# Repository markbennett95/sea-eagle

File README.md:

# BCA Sea Eagle Distortion

A multi-stage distortion pedal designed in conjunction with Nick Earle. The inspiration was a tight, heavy, Fall out boy-style rhythm tone. It features a dual-gang gain pot, an active 3-band EQ, and several pre-gain tone shaping switches. It is powered by our standard +-15V power supply, and uses a series of current sources to bias the various JFET stages.

## v1.0.0-build
1590BB enclosure with pots for Gain, Bass, Middle, Treble, Volume, and switches for bright, tight/fat, and high/low input gain.

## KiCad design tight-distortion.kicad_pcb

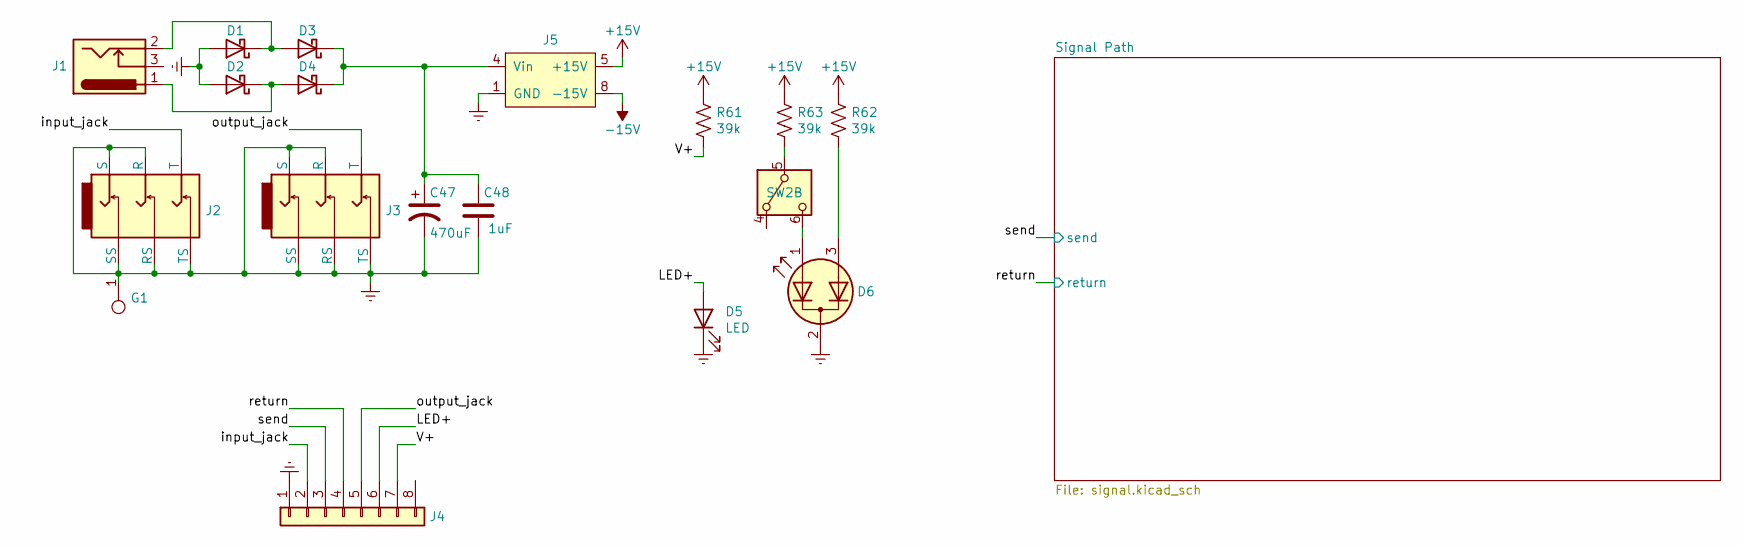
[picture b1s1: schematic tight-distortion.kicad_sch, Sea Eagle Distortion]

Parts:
C47: 470uF; CP_Radial_D8.0mm_P3.50mm
C48: 1uF; C_0805_2012Metric_Pad1.18x1.45mm_HandSolder
D1, D2, D3, D4: 1N5819; D_SOD-123
D5: LED; LED_D5.0mm
D6: LED_Dual_AAK; LED_D5.0mm-3
G1: GNDSpring; Keystone_628
J1: Barrel_Jack_Switch; DC_Jack_DC005
J2, J3: AudioJack_TRS; Rean_NYS215
J4: Conn_01x08; Pin_Header_Straight_1x08_Pitch2.54mm
J5: power-module; Power-module
R61, R62, R63: 39k; R_L3.6mm_D1.6mm_P5.00mm_Horizontal
SW2: SW_DPDT_x2; Pin_Header_Straight_1x06_Pitch2.54mm

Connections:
+15V: J5.5 (+15V), R61.1, R62.1, R63.1; also elsewhere on the board
-15V: J5.8 (-15V); also elsewhere on the board
/LED+: D5.2 (A), J4.6
/V+: J4.7, R61.2
/input_jack: J2.1 (T), J4.2
/output_jack: J3.1 (T), J4.5
/return: J4.4; also elsewhere on the board
/send: J4.3; also elsewhere on the board
Earth: C47.2, C48.2, D1.2 (A), D2.2 (A), D5.1 (K), D6.2 (K), G1.1, J2.2 (R), J2.3 (S), J2.4 (TS), J2.5 (RS), J2.6 (SS), J3.2 (R), J3.3 (S), J3.4 (TS), J3.5 (RS), J3.6 (SS), J4.1, J5.1 (GND); also elsewhere on the board
unnamed: D1.1 (K), D3.2 (A), J1.2
unnamed: D2.1 (K), D4.2 (A), J1.1
unnamed: C47.1, C48.1, D3.1 (K), D4.1 (K), J5.4 (Vin)
unnamed: D6.1 (A1), SW2.6 (C)
unnamed: D6.3 (A2), R62.2
unnamed: R63.2, SW2.5 (B)

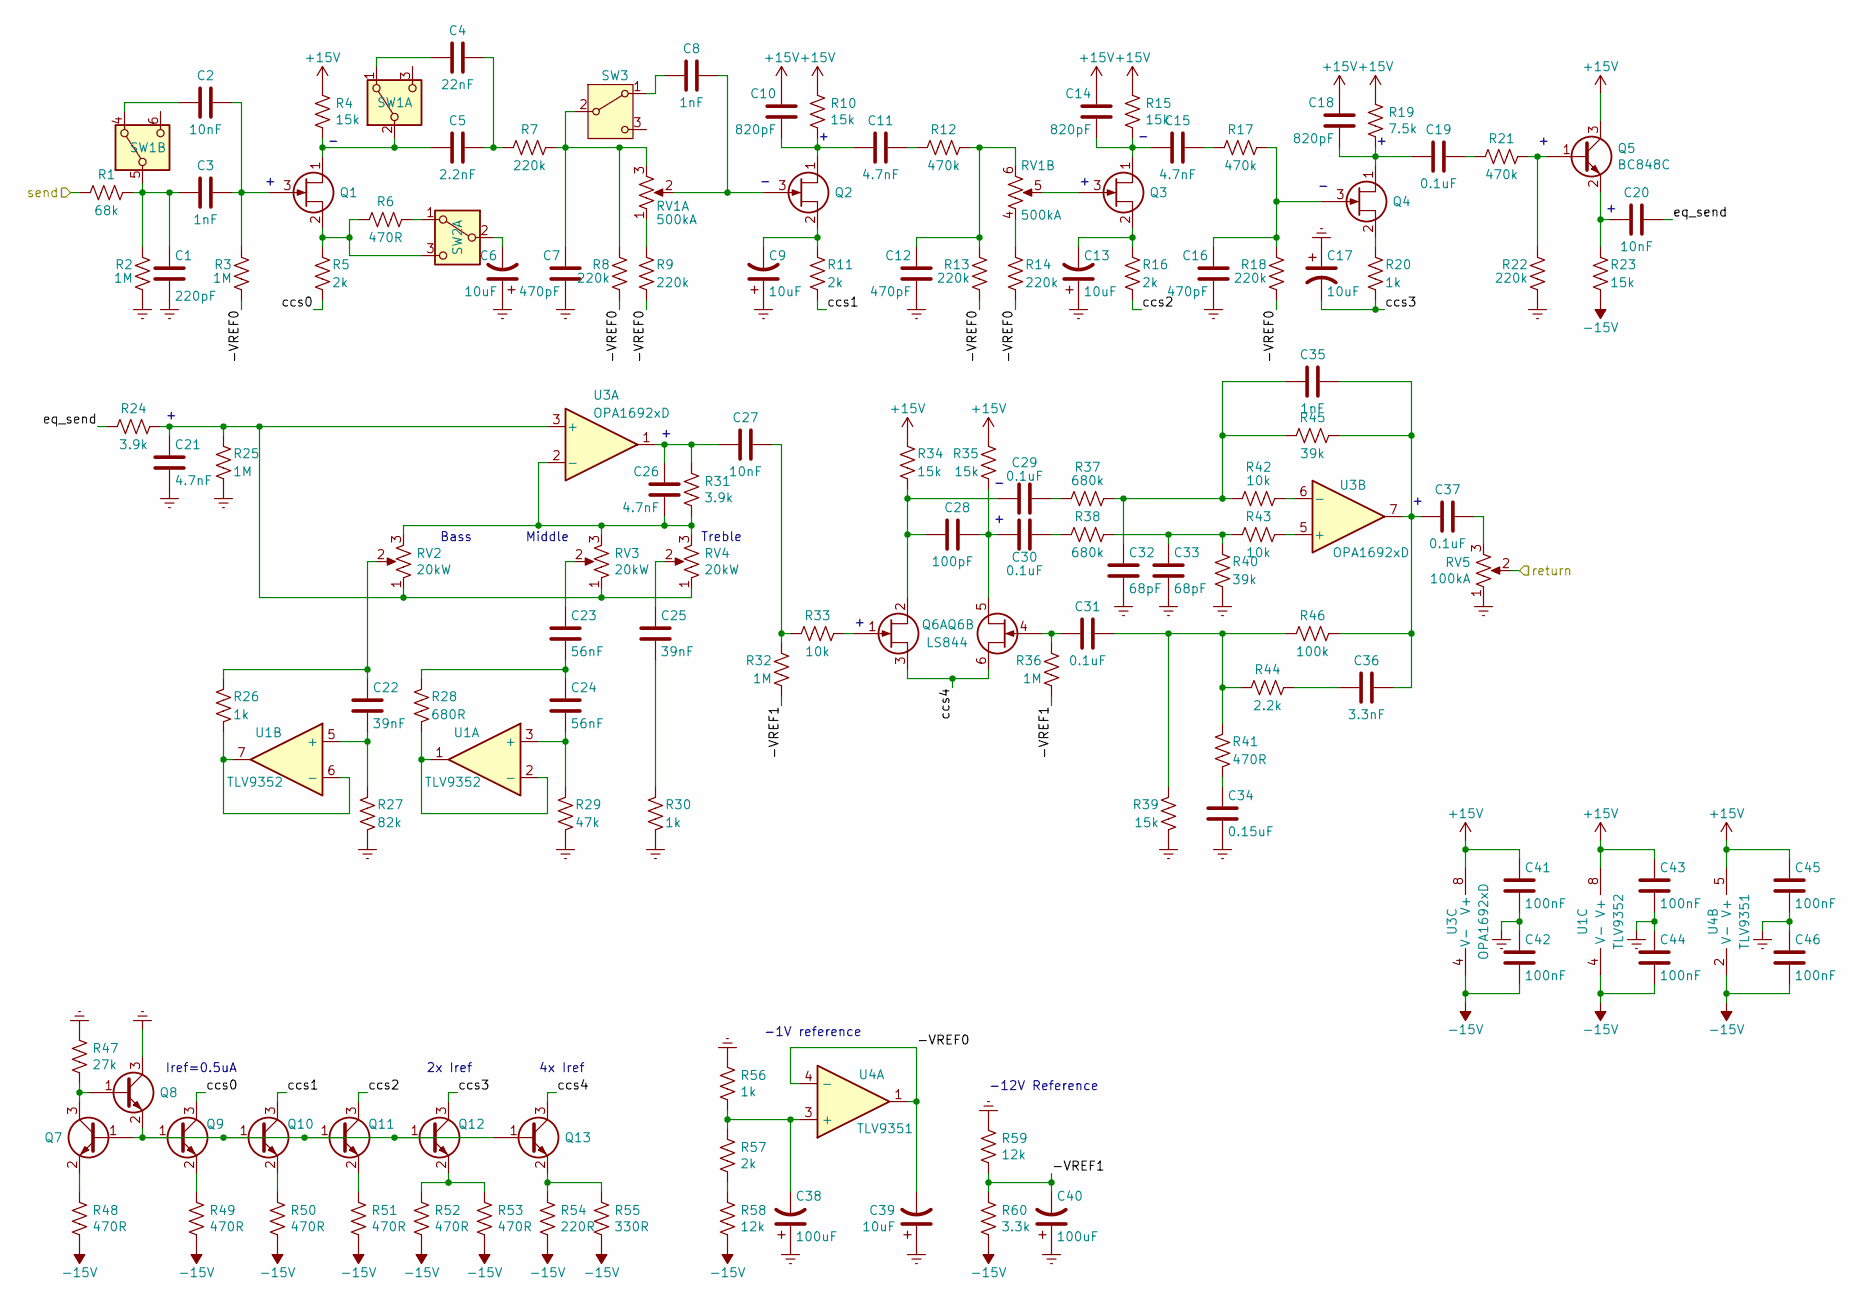
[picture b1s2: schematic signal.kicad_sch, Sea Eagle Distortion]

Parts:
C1: 220pF; C_0603_1608Metric_Pad1.08x0.95mm_HandSolder
C2, C20, C27: 10nF; C_Film_L7.2mm_W2.5mm_P5.00mm
C3, C8, C35: 1nF; C_Film_L7.2mm_W2.5mm_P5.00mm
C4: 22nF; C_Film_L7.2mm_W2.5mm_P5.00mm
C5: 2.2nF; C_Film_L7.2mm_W2.5mm_P5.00mm
C6, C9, C13, C17, C39: 10uF; CP_Radial_D4.0mm_P1.50mm
C7, C12, C16: 470pF; C_0603_1608Metric_Pad1.08x0.95mm_HandSolder
C10, C14, C18: 820pF; C_0603_1608Metric_Pad1.08x0.95mm_HandSolder
C11, C15, C21, C26: 4.7nF; C_Film_L7.2mm_W2.5mm_P5.00mm
C19, C29, C30, C31, C37: 0.1uF; C_Film_L7.2mm_W2.5mm_P5.00mm
C22, C25: 39nF; C_Film_L7.2mm_W2.5mm_P5.00mm
C23, C24: 56nF; C_Film_L7.2mm_W2.5mm_P5.00mm
C28: 100pF; C_0603_1608Metric_Pad1.08x0.95mm_HandSolder
C32, C33: 68pF; C_0603_1608Metric_Pad1.08x0.95mm_HandSolder
C34: 0.15uF; C_Film_L7.2mm_W2.5mm_P5.00mm
C36: 3.3nF; C_Film_L7.2mm_W2.5mm_P5.00mm
C38, C40: 100uF; CP_Radial_D6.3mm_P2.50mm
C41, C42, C43, C44, C45, C46: 100nF; C_0603_1608Metric_Pad1.08x0.95mm_HandSolder
Q1, Q2, Q3, Q4: MMBFJ202; SOT-23_Handsoldering
Q5, Q7, Q8, Q9, Q10, Q11, Q12, Q13: BC848C; SOT-23_Handsoldering
Q6: LS844; SOT-23-6_Handsoldering
R1: 68k; R_L3.6mm_D1.6mm_P5.00mm_Horizontal
R2, R3, R25, R32, R36: 1M; R_L3.6mm_D1.6mm_P5.00mm_Horizontal
R4, R10, R15, R23, R34, R35, R39: 15k; R_L3.6mm_D1.6mm_P5.00mm_Horizontal
R5, R11, R16: 2k; R_L3.6mm_D1.6mm_P5.00mm_Horizontal
R6, R41: 470R; R_L3.6mm_D1.6mm_P5.00mm_Horizontal
R7, R8, R9, R13, R14, R18, R22: 220k; R_L3.6mm_D1.6mm_P5.00mm_Horizontal
R12, R17, R21: 470k; R_L3.6mm_D1.6mm_P5.00mm_Horizontal
R19: 7.5k; R_L3.6mm_D1.6mm_P5.00mm_Horizontal
R20, R26, R30: 1k; R_L3.6mm_D1.6mm_P5.00mm_Horizontal
R24, R31: 3.9k; R_L3.6mm_D1.6mm_P5.00mm_Horizontal
R27: 82k; R_L3.6mm_D1.6mm_P5.00mm_Horizontal
R28: 680R; R_L3.6mm_D1.6mm_P5.00mm_Horizontal
R29: 47k; R_L3.6mm_D1.6mm_P5.00mm_Horizontal
R33, R42, R43: 10k; R_L3.6mm_D1.6mm_P5.00mm_Horizontal
R37, R38: 680k; R_L3.6mm_D1.6mm_P5.00mm_Horizontal
R40, R45: 39k; R_L3.6mm_D1.6mm_P5.00mm_Horizontal
R44: 2.2k; R_L3.6mm_D1.6mm_P5.00mm_Horizontal
R46: 100k; R_L3.6mm_D1.6mm_P5.00mm_Horizontal
R47: 27k; R_0603_1608Metric_Pad0.98x0.95mm_HandSolder
R48, R49, R50, R51, R52, R53: 470R; R_0603_1608Metric_Pad0.98x0.95mm_HandSolder
R54: 220R; R_0603_1608Metric_Pad0.98x0.95mm_HandSolder
R55: 330R; R_0603_1608Metric_Pad0.98x0.95mm_HandSolder
R56: 1k; R_0603_1608Metric_Pad0.98x0.95mm_HandSolder
R57: 2k; R_0603_1608Metric_Pad0.98x0.95mm_HandSolder
R58, R59: 12k; R_0603_1608Metric_Pad0.98x0.95mm_HandSolder
R60: 3.3k; R_0603_1608Metric_Pad0.98x0.95mm_HandSolder
RV1: 500kA; R_POT_DUAL
RV2, RV3, RV4: 20kW; R_POT
RV5: 100kA; R_POT
SW1: SW_DPDT_x2; SW_Toggle_DPDT_SolderLug
SW2: SW_DPDT_x2; Pin_Header_Straight_1x06_Pitch2.54mm
SW3: SW_SPDT; SW_Toggle_SPDT_SolderLug
U1: TLV9352; SOIC-8_3.9x4.9mm_P1.27mm
U3: OPA1692xD; SOIC-8_3.9x4.9mm_P1.27mm
U4: TLV9351; SOT-23-5

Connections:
+15V: C10.2, C14.2, C18.2, C41.1, C43.1, C45.1, Q5.3 (C), R4.1, R10.1, R15.1, R19.1, R34.1, R35.1, U1.8 (V+), U3.8 (V+), U4.5 (V+); also elsewhere on the board
-15V: C42.2, C44.2, C46.2, R23.2, R48.2, R49.2, R50.2, R51.2, R52.2, R53.2, R54.2, R55.2, R58.2, R60.2, U1.4 (V-), U3.4 (V-), U4.2 (V-); also elsewhere on the board
/Signal Path/-VREF0: C39.2, R3.2, R8.2, R9.2, R13.2, R14.2, R18.2, U4.1, U4.4 (-)
/Signal Path/-VREF1: C40.2, R32.2, R36.2, R59.2, R60.1
/Signal Path/ccs0: Q9.3 (C), R5.2
/Signal Path/ccs1: Q10.3 (C), R11.2
/Signal Path/ccs2: Q11.3 (C), R16.2
/Signal Path/ccs3: C17.2, Q12.3 (C), R20.2
/Signal Path/ccs4: Q6.3 (S1), Q6.6 (S1), Q13.3 (C)
/Signal Path/eq_send: C20.1, R24.1
/return: RV5.2; also elsewhere on the board
/send: R1.1; also elsewhere on the board
Earth: C1.2, C6.1, C7.1, C9.1, C12.1, C13.1, C16.1, C17.1, C21.1, C32.1, C33.1, C34.2, C38.1, C39.1, C40.1, C41.2, C42.1, C43.2, C44.1, C45.2, C46.1, Q8.3 (C), R2.2, R22.2, R25.2, R27.2, R29.2, R30.2, R39.2, R40.2, R47.1, R56.1, R59.1, RV5.1; also elsewhere on the board
unnamed: C4.1, C5.1, R7.1
unnamed: C11.1, R12.1
unnamed: C12.2, R12.2, R13.1, RV1.6
unnamed: C15.1, R17.1
unnamed: C19.1, R21.1
unnamed: C22.1, R26.1, RV2.2
unnamed: C23.1, RV3.2
unnamed: C23.2, C24.1, R28.1
unnamed: C25.1, RV4.2
unnamed: C25.2, R30.1
unnamed: C26.2, C27.2, R31.1, U3.1
unnamed: C27.1, R32.1, R33.1
unnamed: C29.1, R37.1
unnamed: C30.1, R38.1
unnamed: C31.1, R39.1, R41.1, R44.1, R46.1
unnamed: C32.2, C35.1, R37.2, R42.1, R45.1
unnamed: C33.2, R38.2, R40.1, R43.1
unnamed: C34.1, R41.2
unnamed: C35.2, C36.1, C37.2, R45.2, R46.2, U3.7
unnamed: C36.2, R44.2
unnamed: C37.1, RV5.3
unnamed: C5.2, Q1.1 (D), R4.2, SW1.2 (B)
unnamed: C2.1, C3.1, Q1.3 (G), R3.1
unnamed: Q1.2 (S), R5.1, R6.1, SW2.3 (C)
unnamed: C10.1, C11.2, Q2.1 (D), R10.2
unnamed: C8.1, Q2.3 (G), RV1.2 (5)
unnamed: C9.2, Q2.2 (S), R11.1
unnamed: C14.1, C15.2, Q3.1 (D), R15.2
unnamed: Q3.3 (G), RV1.5
unnamed: C13.2, Q3.2 (S), R16.1
unnamed: C18.1, C19.2, Q4.1 (D), R19.2
unnamed: C16.2, Q4.3 (G), R17.2, R18.1
unnamed: Q4.2 (S), R20.1
unnamed: Q5.1 (B), R21.2, R22.1
unnamed: C20.2, Q5.2 (E), R23.1
unnamed: C28.1, C29.2, Q6.2 (D1), R34.2
unnamed: Q6.1 (G1), R33.2
unnamed: C28.2, C30.2, Q6.5 (D2), R35.2
unnamed: C31.2, Q6.4 (G1), R36.1
unnamed: Q7.3 (C), Q8.1 (B), R47.2
unnamed: Q7.2 (E), R48.1
unnamed: Q9.2 (E), R49.1
unnamed: Q7.1 (B), Q8.2 (E), Q9.1 (B), Q10.1 (B), Q11.1 (B), Q12.1 (B), Q13.1 (B)
unnamed: Q10.2 (E), R50.1
unnamed: Q11.2 (E), R51.1
unnamed: Q12.2 (E), R52.1, R53.1
unnamed: Q13.2 (E), R54.1, R55.1
unnamed: R14.1, RV1.4
unnamed: R57.2, R58.1
unnamed: R9.1, RV1.1 (4)
unnamed: C7.2, R7.2, R8.1, RV1.3 (6), SW3.2 (B)
unnamed: C4.2, SW1.1 (A)
unnamed: C2.2, SW1.4 (A)
unnamed: C1.1, C3.2, R1.2, R2.1, SW1.5 (B)
unnamed: R6.2, SW2.1 (A)
unnamed: C6.2, SW2.2 (B)
unnamed: C8.2, SW3.1 (A)
unnamed: C24.2, R29.1, U1.3 (+)
unnamed: R28.2, U1.1, U1.2 (-)
unnamed: C22.2, R27.1, U1.5 (+)
unnamed: R26.2, U1.6 (-), U1.7
unnamed: C21.2, R24.2, R25.1, RV2.1, RV3.1, RV4.1, U3.3 (+)
unnamed: C26.1, R31.2, RV2.3, RV3.3, RV4.3, U3.2 (-)
unnamed: R43.2, U3.5 (+)
unnamed: R42.2, U3.6 (-)
unnamed: C38.2, R56.2, R57.1, U4.3 (+)

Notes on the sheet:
4x Iref
Treble
2x Iref
Bass
-1V reference
Iref=0.5uA
-12V Reference
Middle

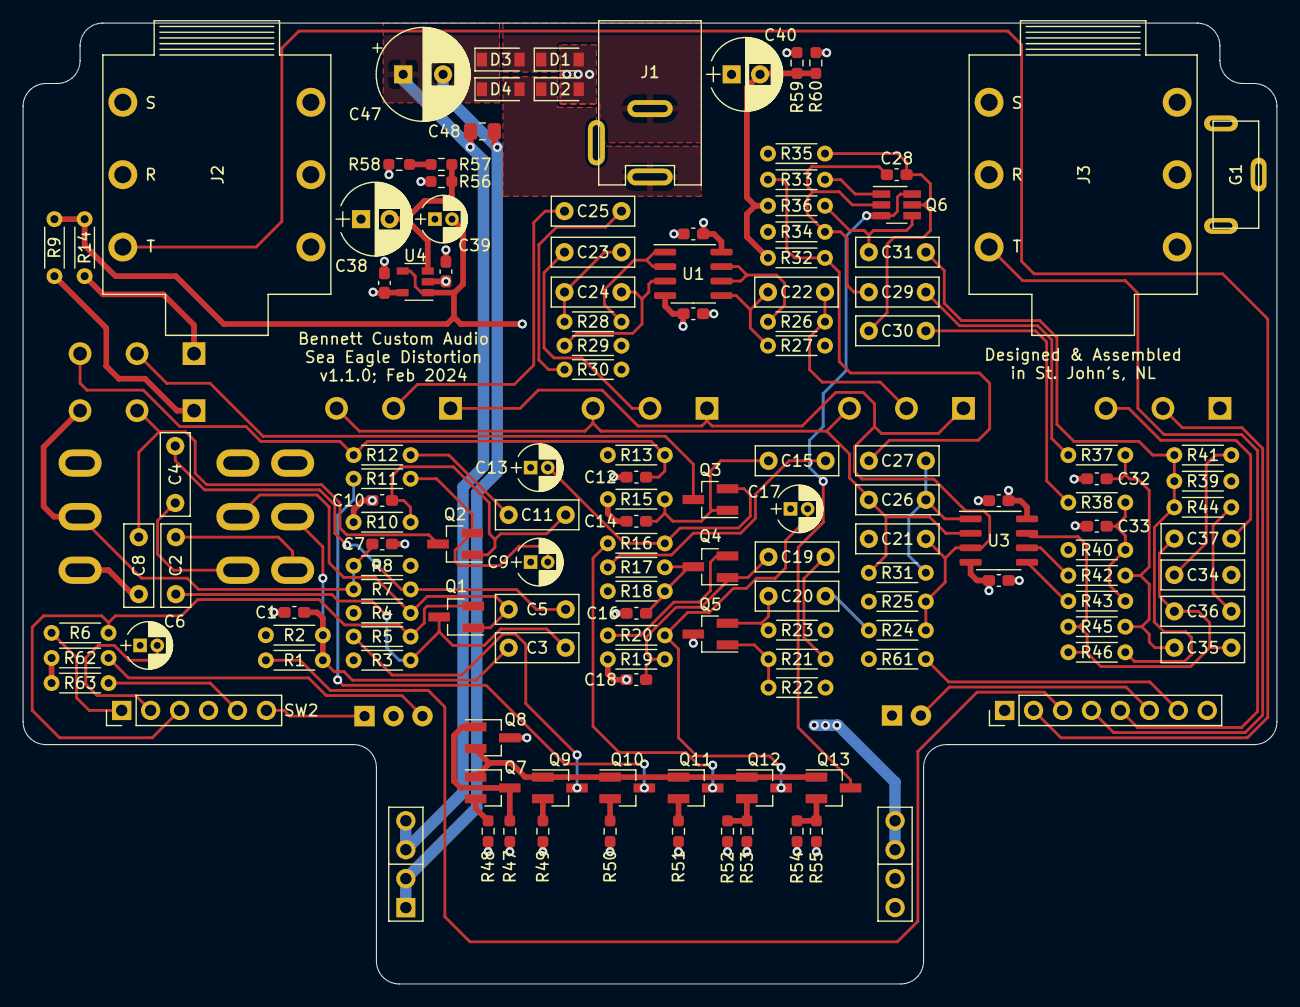
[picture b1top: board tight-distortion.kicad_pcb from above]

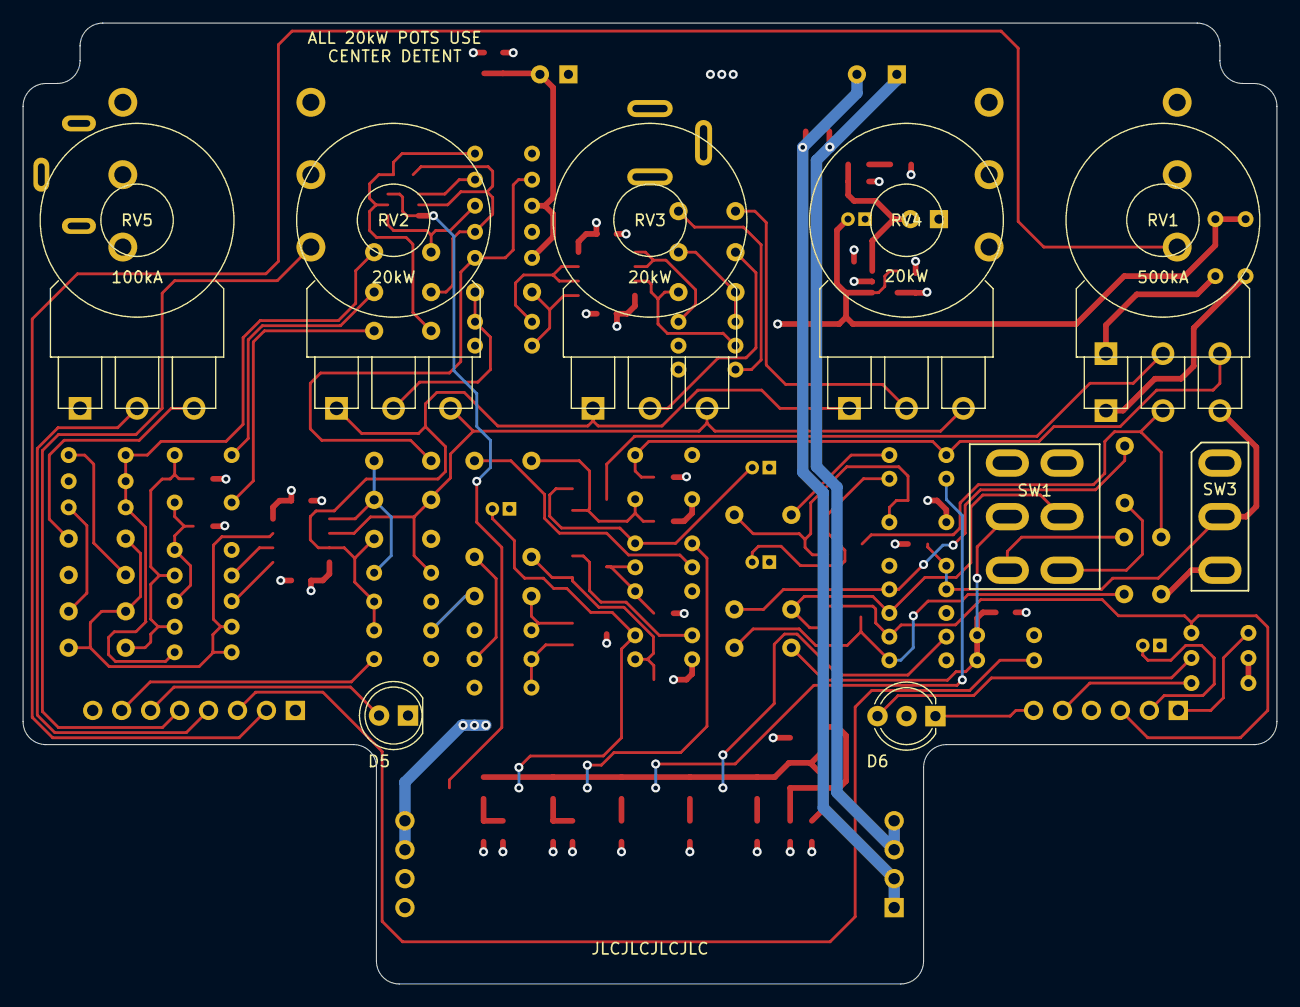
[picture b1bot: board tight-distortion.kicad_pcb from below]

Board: 4 copper layers, 110.0 x 84.3 mm, 147 parts (4 on the bottom side), 89 nets.

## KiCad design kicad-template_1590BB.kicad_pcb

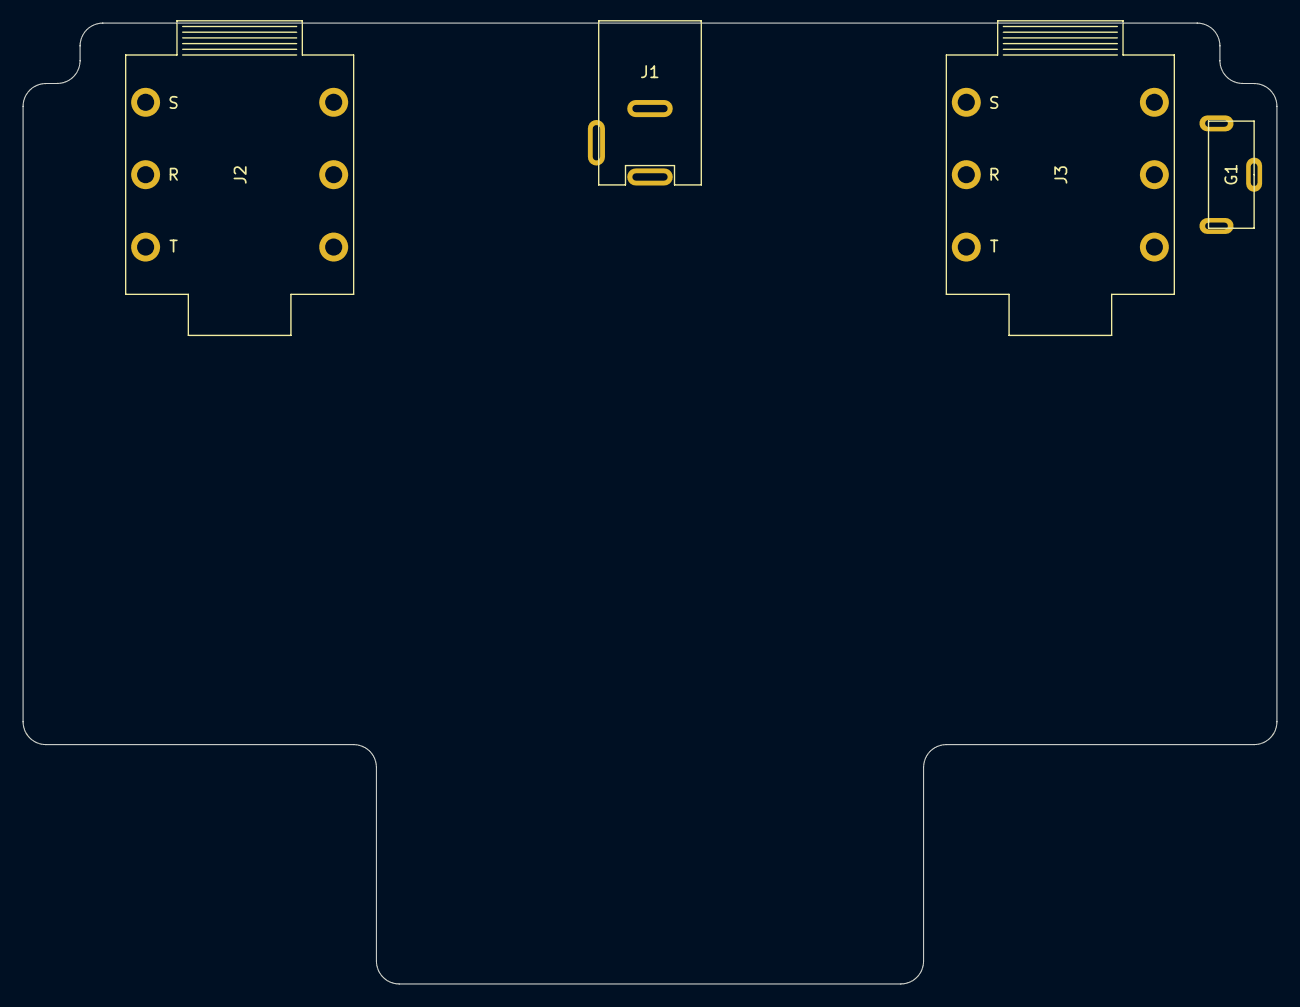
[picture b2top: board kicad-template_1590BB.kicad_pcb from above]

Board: 2 copper layers, 110.0 x 84.3 mm, 4 parts (0 on the bottom side), 2 nets, no tracks yet.

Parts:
G1: GNDSpring; Keystone_628
J1: Barrel_Jack_Switch; DC_Jack_DC005
J2, J3: AudioJack_TRS; Rean_NYS215

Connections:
Earth: G1.1, J2.3, J2.4, J2.6, J3.2, J3.3, J3.4, J3.5, J3.6
unnamed: J1.1, J2.2

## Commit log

2023-06-12 updated file names
2023-12-05 initial idea
2023-12-09 first schematic draft
2023-12-10 first PCB layout draft
2023-12-11 first pass of routing PCB
2023-12-11 corrected & finalized PCB
2023-12-12 gerbers
2024-01-12 development checkpoint
2024-01-24 as built with current PCB
2024-02-02 updated .gitignore for new file types
2024-02-02 updated project with new file formats
2024-02-02 updated gitignore
2024-02-02 start of PCB re-route
2024-02-07 first draft of PCB
2024-02-07 small schematic change
2024-02-16 final look at PCB
2024-02-16 generate gerbers
